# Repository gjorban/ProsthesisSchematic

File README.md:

ProsthesisSchematic
===================

Schematics for Prosthesis PCBs

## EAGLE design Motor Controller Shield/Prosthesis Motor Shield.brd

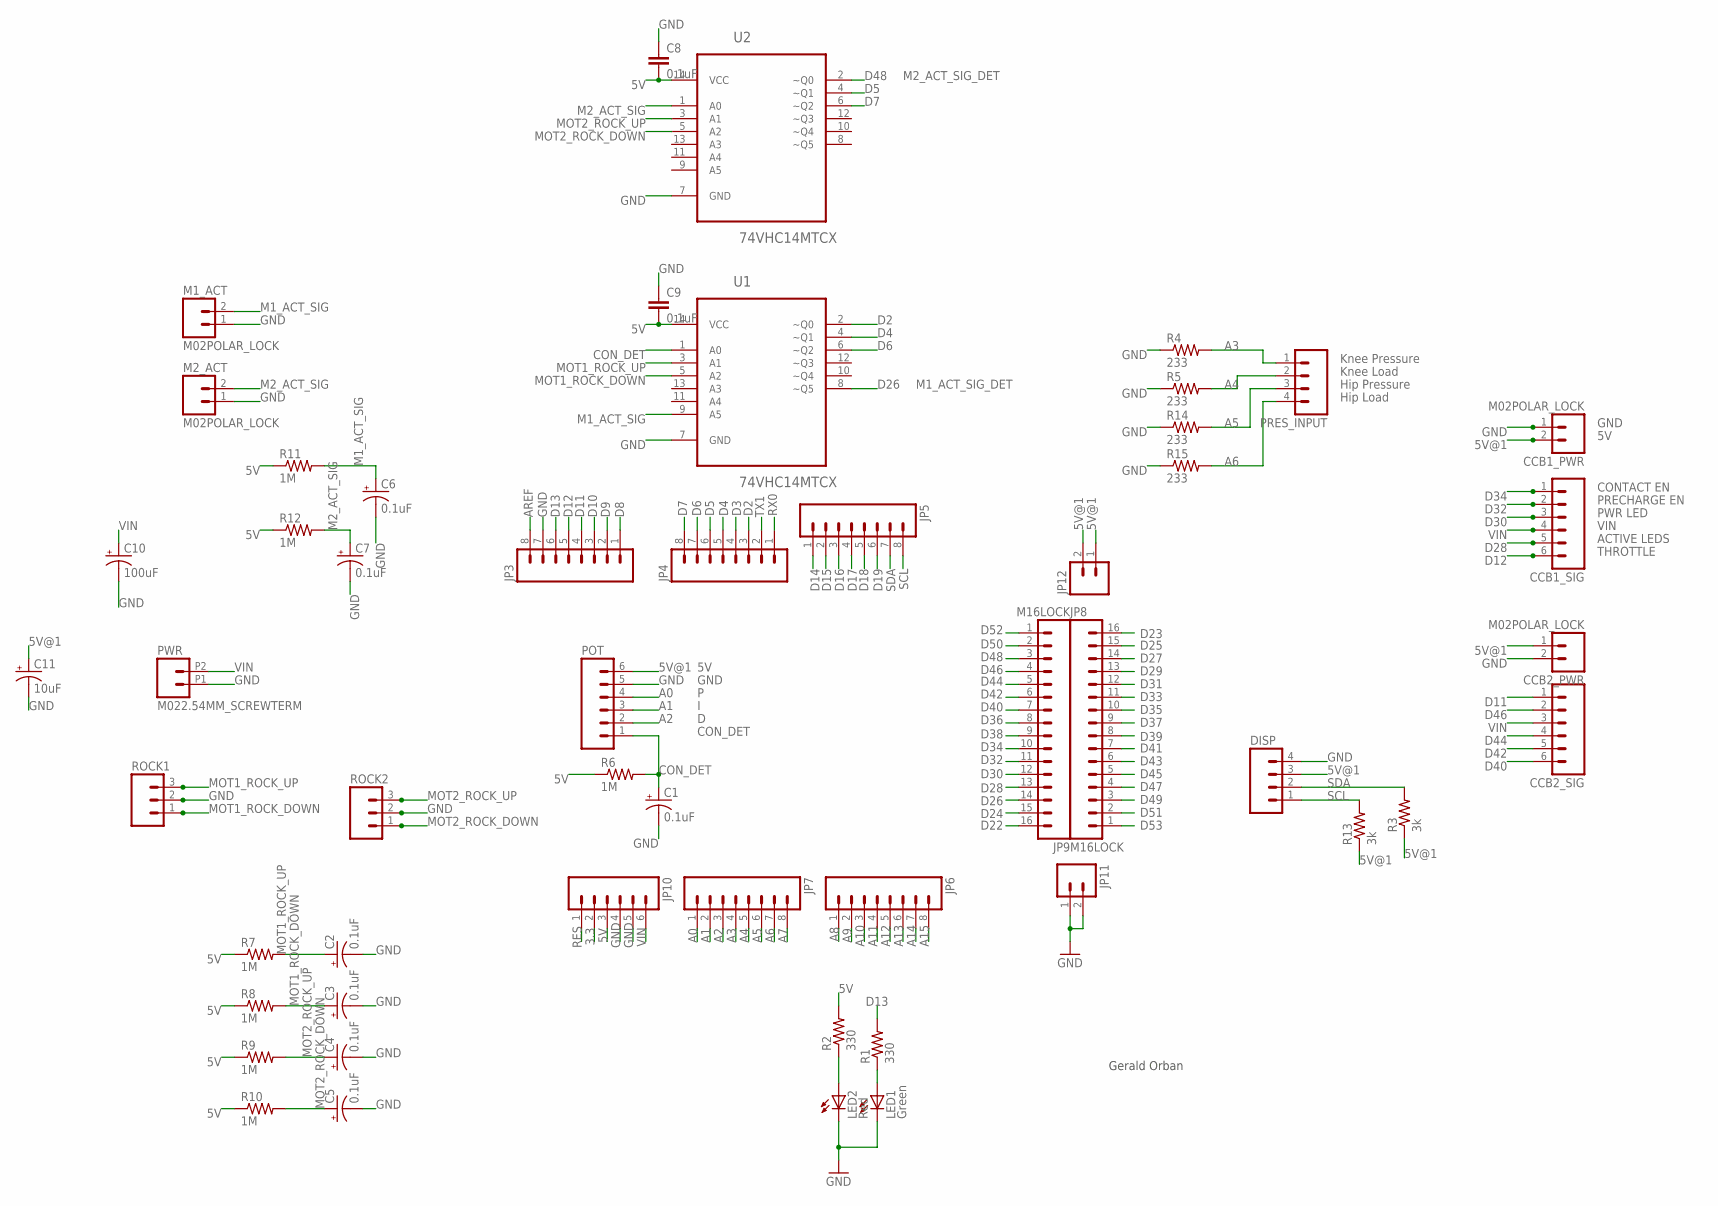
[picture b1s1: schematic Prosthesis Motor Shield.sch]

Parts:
C1, C2, C3, C4, C5, C6, C7: 0.1uF; EIA3216
C8, C9: 0.1uF; 0603-CAP
C10: 100uF; CPOL-RADIAL-100UF-25V
C11: 10uF; CPOL-RADIAL-10UF-25V
CCB1_PWR, CCB2_PWR: M02POLAR_LOCK; MOLEX-1X2_LOCK
CCB1_SIG, CCB2_SIG: M06POLAR_LOCK; MOLEX-1X6_LOCK
DISP: M04POLAR_LOCK; MOLEX-1X4_LOCK
JP3, JP4, JP5, JP6, JP7: M08LOCK; 1X08_LOCK
JP8, JP9: M16LOCK; 1X16_LOCK
JP10: M06LOCK; 1X06_LOCK
JP11, JP12: M02LOCK; 1X02_LOCK
LED1: Green; LED-1206
LED2: Red; LED-1206
M1_ACT, M2_ACT: M02POLAR_LOCK; MOLEX-1X2_LOCK
POT: M06POLAR_LOCK; MOLEX-1X6_LOCK
PRES_INPUT: M04POLAR_LOCK; MOLEX-1X4_LOCK
PWR: M022.54MM_SCREWTERM; 1X02_2.54_SCREWTERM
R1, R2: 330; 0805
R3, R13: 3k; 0603-RES
R4, R5, R14, R15: 233; AXIAL-0.4
R6, R7, R8, R9, R10, R11, R12: 1M; 0603-RES
ROCK1, ROCK2: M03POLAR_LOCK; MOLEX-1X3_LOCK
U1, U2: 74VHC14MTCX; SOP65P640X120-14N

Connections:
3.3: JP10.2
5V: C8.2, C9.2, JP10.3, R2.2, R6.1, R7.1, R8.1, R9.1, R10.1, R11.1, R12.1, U1.14 (VCC), U2.14 (VCC)
5V@1: C11.1 (+), CCB1_PWR.2, CCB2_PWR.1, DISP.3, JP12.1, JP12.2, POT.6, R3.1, R13.1
A0: JP7.1, POT.4
A1: JP7.2, POT.3
A2: JP7.3, POT.2
A3: JP7.4, PRES_INPUT.1, R4.P$2 (2)
A4: JP7.5, PRES_INPUT.2, R5.P$2 (2)
A5: JP7.6, PRES_INPUT.3, R14.P$2 (2)
A6: JP7.7, PRES_INPUT.4, R15.P$2 (2)
A7: JP7.8
A8: JP6.1
A9: JP6.2
A10: JP6.3
A11: JP6.4
A12: JP6.5
A13: JP6.6
A14: JP6.7
A15: JP6.8
AREF: JP3.8
CON_DET: C1.A (+), POT.1, R6.2, U1.1 (A0)
D2: JP4.3, U1.2 (~Q0)
D3: JP4.4
D4: JP4.5, U1.4 (~Q1)
D5: JP4.6, U2.4 (~Q1)
D6: JP4.7, U1.6 (~Q2)
D7: JP4.8, U2.6 (~Q2)
D8: JP3.1
D9: JP3.2
D10: JP3.3
D11: CCB2_SIG.1, JP3.4
D12: CCB1_SIG.6, JP3.5
D13: JP3.6, R1.2
D14: JP5.1
D15: JP5.2
D16: JP5.3
D17: JP5.4
D18: JP5.5
D19: JP5.6
D22: JP9.16
D23: JP8.16
D24: JP9.15
D25: JP8.15
D26: JP9.14, U1.8 (~Q5)
D27: JP8.14
D28: CCB1_SIG.5, JP9.13
D29: JP8.13
D30: CCB1_SIG.3, JP9.12
D31: JP8.12
D32: CCB1_SIG.2, JP9.11
D33: JP8.11
D34: CCB1_SIG.1, JP9.10
D35: JP8.10
D36: JP9.9
D37: JP8.9
D38: JP9.8
D39: JP8.8
D40: CCB2_SIG.6, JP9.7
D41: JP8.7
D42: CCB2_SIG.5, JP9.6
D43: JP8.6
D44: CCB2_SIG.4, JP9.5
D45: JP8.5
D46: CCB2_SIG.2, JP9.4
D47: JP8.4
D48: JP9.3, U2.2 (~Q0)
D49: JP8.3
D50: JP9.2
D51: JP8.2
D52: JP9.1
D53: JP8.1
GND: C1.C (-), C2.C (-), C3.C (-), C4.C (-), C5.C (-), C6.C (-), C7.C (-), C8.1, C9.1, C10.2 (-), C11.2 (-), CCB1_PWR.1, CCB2_PWR.2, DISP.4, JP3.7, JP10.4, JP10.5, JP11.1, JP11.2, LED1.C, LED2.C, M1_ACT.1, M2_ACT.1, POT.5, PWR.P1 (1), R4.P$1 (1), R5.P$1 (1), R14.P$1 (1), R15.P$1 (1), ROCK1.2, ROCK2.2, U1.7 (GND), U2.7 (GND)
M1_ACT_SIG: C6.A (+), M1_ACT.2, R11.2, U1.9 (A5)
M2_ACT_SIG: C7.A (+), M2_ACT.2, R12.2, U2.1 (A0)
MOT1_ROCK_DOWN: C3.A (+), R8.2, ROCK1.1, U1.5 (A2)
MOT1_ROCK_UP: C2.A (+), R7.2, ROCK1.3, U1.3 (A1)
MOT2_ROCK_DOWN: C5.A (+), R10.2, ROCK2.1, U2.5 (A2)
MOT2_ROCK_UP: C4.A (+), R9.2, ROCK2.3, U2.3 (A1)
unnamed: LED2.A, R2.1
unnamed: LED1.A, R1.1
RES: JP10.1
RX0: JP4.1
SCL: DISP.1, JP5.8, R13.2
SDA: DISP.2, JP5.7, R3.2
TX1: JP4.2
VIN: C10.1 (+), CCB1_SIG.4, CCB2_SIG.3, JP10.6, PWR.P2 (2)

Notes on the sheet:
Gerald Orban
THROTTLE
ACTIVE LEDS
VIN
PWR LED
PRECHARGE EN
CONTACT EN
GND
CON_DET
Knee Pressure
Knee Load
Hip Pressure
Hip Load
M2_ACT_SIG_DET
M1_ACT_SIG_DET

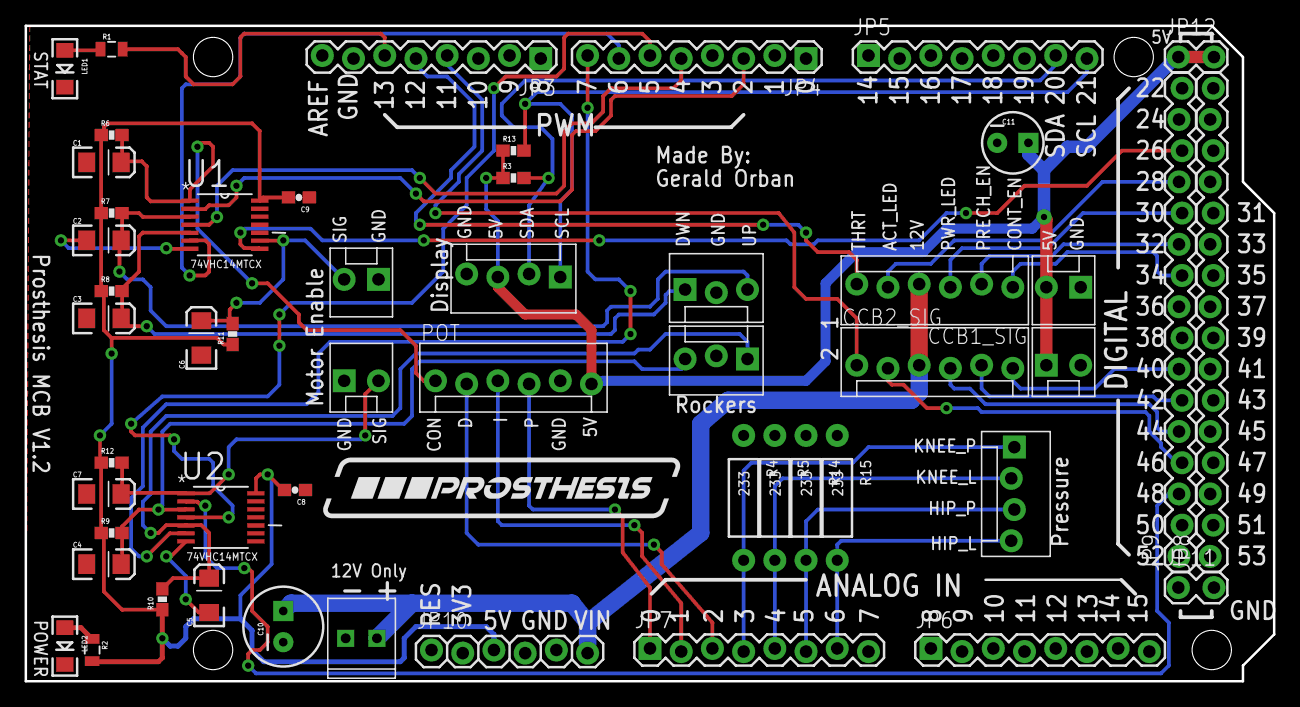
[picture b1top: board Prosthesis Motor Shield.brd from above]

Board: 2 copper layers, 101.6 x 53.3 mm, 53 parts (0 on the bottom side), 40 nets.

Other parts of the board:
U$1: PROS_LOGO

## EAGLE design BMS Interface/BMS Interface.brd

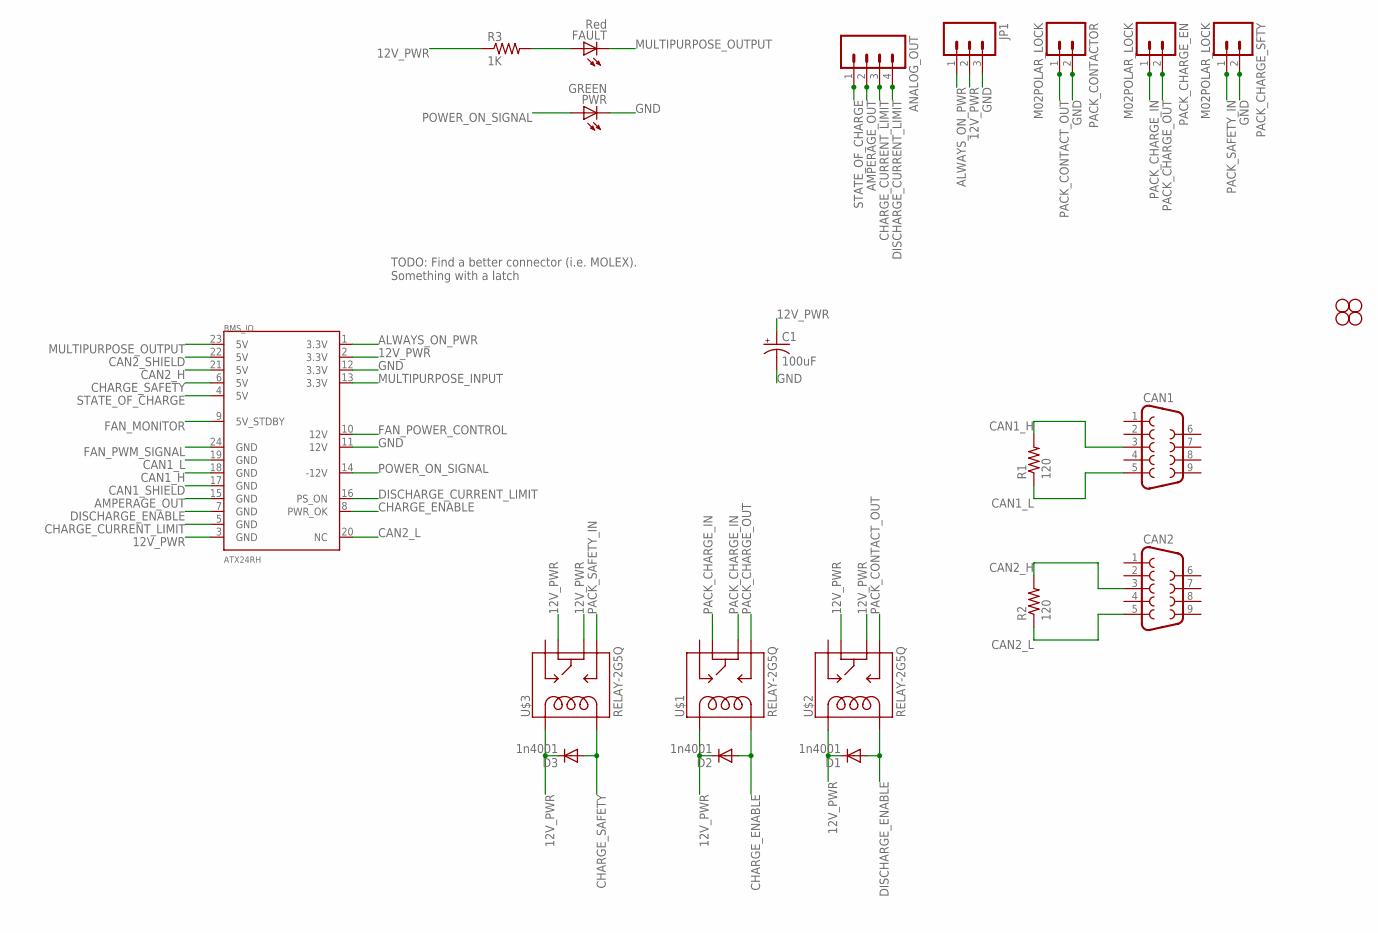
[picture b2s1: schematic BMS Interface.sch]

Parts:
ANALOG_OUT: M04POLAR_LOCK; MOLEX-1X4_LOCK
BMS_IO: ATX24RH; ATX24_RIGHT_ANGLE
C1: 100uF; CPOL-RADIAL-100UF-25V
CAN1, CAN2: DB9FEMALE; DB9
D1, D2, D3: 1n4001; SMA-DIODE
FAULT: Red; LED5MM
JP1: M03SCREW; SCREWTERMINAL-3.5MM-3
PACK_CHARGE_EN: M02POLAR_LOCK; MOLEX-1X2_LOCK
PACK_CHARGE_SFTY: M02POLAR_LOCK; MOLEX-1X2_LOCK
PACK_CONTACTOR: M02POLAR_LOCK; MOLEX-1X2_LOCK
PWR: GREEN; LED5MM
R1, R2: 120; 0603-RES
R3: 1K; 0805
STANDOFF1, STANDOFF2, STANDOFF3, STANDOFF4: STAND-OFF
U$1, U$2, U$3: RELAY-2G5Q; RELAY-G5V

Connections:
12V_PWR: BMS_IO.2 (3.3V), BMS_IO.3 (GND), C1.1 (+), D1.C, D2.C, D3.C, JP1.2, R3.1, U$1.2, U$2.2, U$2.5, U$2.6, U$3.2, U$3.5, U$3.6
ALWAYS_ON_PWR: BMS_IO.1 (3.3V), JP1.1
AMPERAGE_OUT: ANALOG_OUT.2, BMS_IO.15 (GND)
CAN1_H: BMS_IO.18 (GND), CAN1.3, R1.2
CAN1_L: BMS_IO.19 (GND), CAN1.5, R1.1
CAN1_SHIELD: BMS_IO.17 (GND)
CAN2_H: BMS_IO.21 (5V), CAN2.3, R2.2
CAN2_L: BMS_IO.20 (NC), CAN2.5, R2.1
CAN2_SHIELD: BMS_IO.22 (5V)
CHARGE_CURRENT_LIMIT: ANALOG_OUT.3, BMS_IO.5 (GND)
CHARGE_ENABLE: BMS_IO.8 (PWR_OK), D2.A, U$1.9
CHARGE_SAFETY: BMS_IO.6 (5V), D3.A, U$3.9
DISCHARGE_CURRENT_LIMIT: ANALOG_OUT.4, BMS_IO.16 (PS_ON)
DISCHARGE_ENABLE: BMS_IO.7 (GND), D1.A, U$2.9
FAN_MONITOR: BMS_IO.9 (5V_STDBY)
FAN_POWER_CONTROL: BMS_IO.10 (12V)
FAN_PWM_SIGNAL: BMS_IO.24 (GND)
GND: BMS_IO.11 (12V), BMS_IO.12 (3.3V), C1.2 (-), JP1.3, PACK_CHARGE_SFTY.2, PACK_CONTACTOR.2, PWR.K (C)
MULTIPURPOSE_INPUT: BMS_IO.13 (3.3V)
MULTIPURPOSE_OUTPUT: BMS_IO.23 (5V), FAULT.K (C)
unnamed: FAULT.A, R3.2
PACK_CHARGE_IN: PACK_CHARGE_EN.1, U$1.5, U$1.6
PACK_CHARGE_OUT: PACK_CHARGE_EN.2, U$1.10
PACK_CONTACT_OUT: PACK_CONTACTOR.1, U$2.10
PACK_SAFETY_IN: PACK_CHARGE_SFTY.1, U$3.10
POWER_ON_SIGNAL: BMS_IO.14 (-12V), PWR.A
STATE_OF_CHARGE: ANALOG_OUT.1, BMS_IO.4 (5V)

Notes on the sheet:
TODO: Find a better connector (i.e. MOLEX). Something with a latch

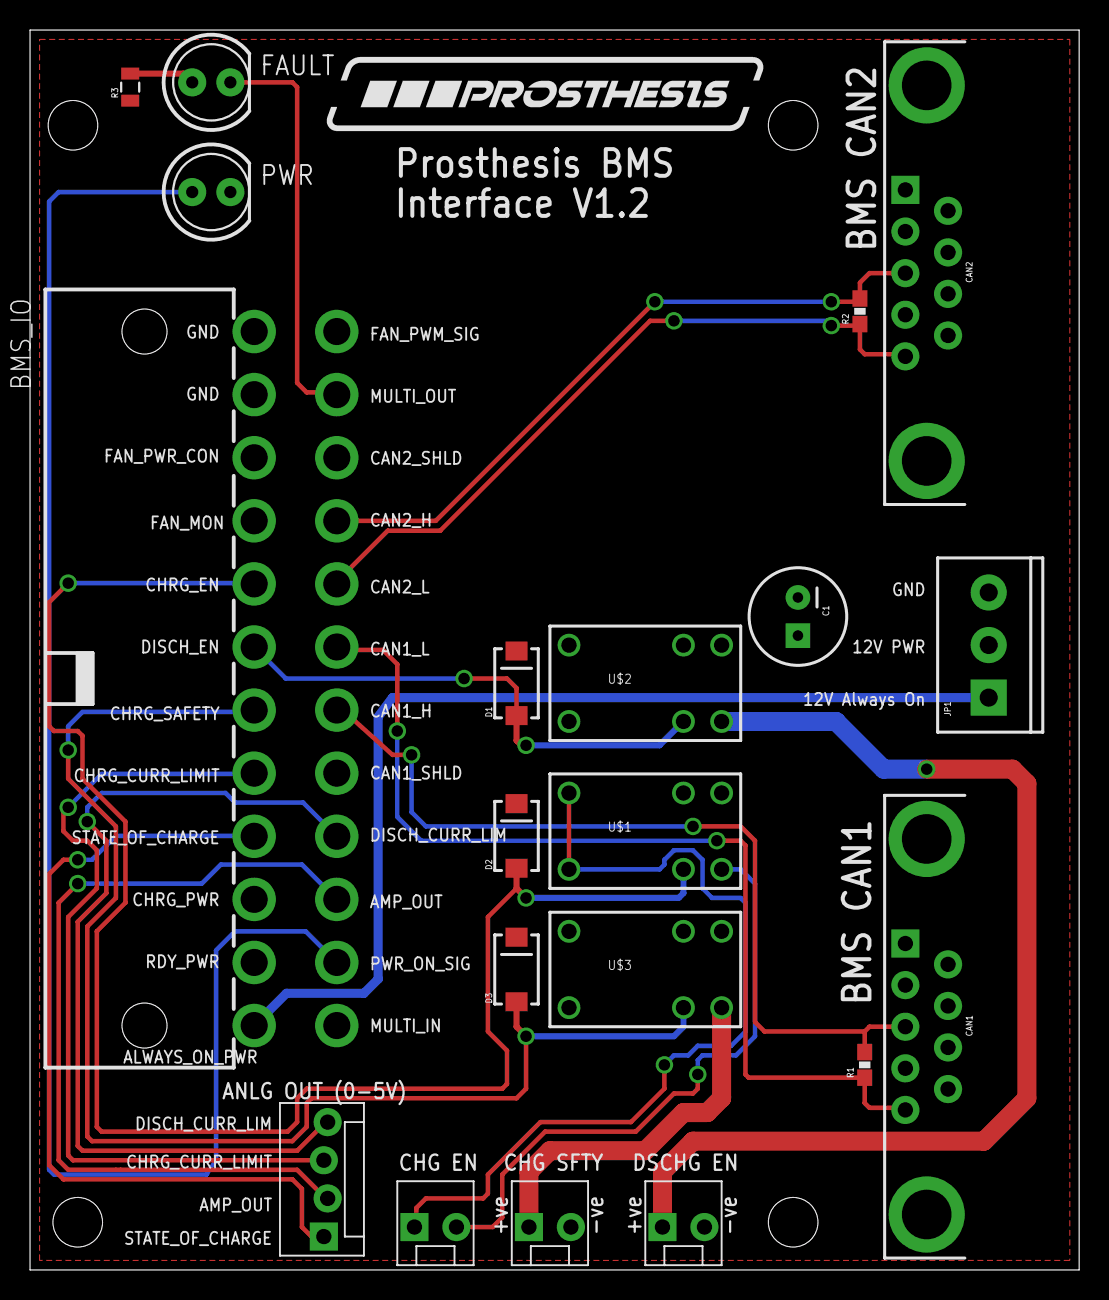
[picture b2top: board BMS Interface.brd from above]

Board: 2 copper layers, 69.8 x 82.5 mm, 25 parts (0 on the bottom side), 21 nets.

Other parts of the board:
U$4: PROS_LOGO

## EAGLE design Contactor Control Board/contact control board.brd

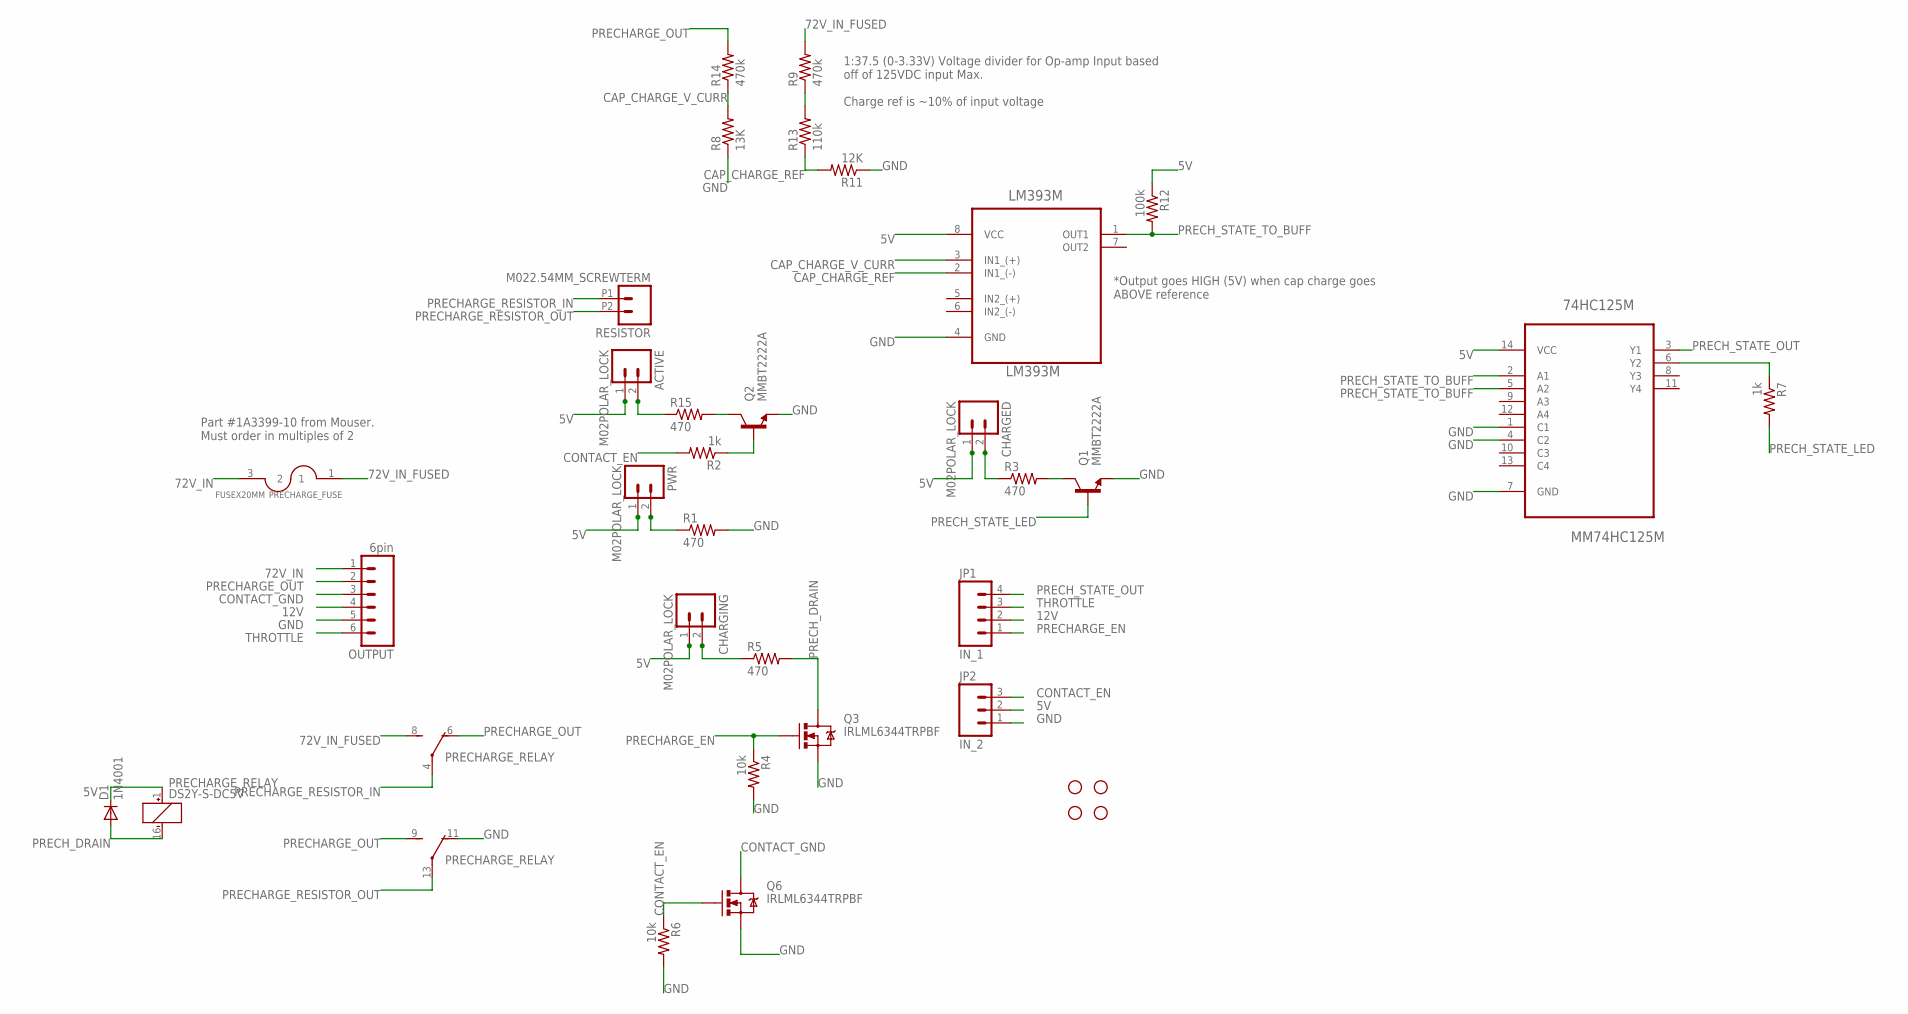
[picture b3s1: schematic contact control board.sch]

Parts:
74HC125M: MM74HC125M; SOIC127P600X175-14N
ACTIVE: M02POLAR_LOCK; MOLEX-1X2_LOCK
CHARGED: M02POLAR_LOCK; MOLEX-1X2_LOCK
CHARGING: M02POLAR_LOCK; MOLEX-1X2_LOCK
D1: 1N4001; DIODE-1N4001
JP1: IN_1; MOLEX-1X4_LOCK
JP2: IN_2; MOLEX-1X3_LOCK
LM393M: LM393M; SOIC127P600X180-8N
OUTPUT: 6pin; SCREWTERMINAL-3.5MM-6
PRECHARGE_FUSE: FUSEX20MM; FUSE_5MM
PRECHARGE_RELAY: DS2Y-S-DC5V; DS2Y
PWR: M02POLAR_LOCK; MOLEX-1X2_LOCK
Q1, Q2: MMBT2222A; SOT23
Q3, Q6: IRLML6344TRPBF; SOT23
R1, R3, R5, R15: 470; 0805
R2, R7: 1k; 0603-RES
R4, R6: 10k; 0603-RES
R8: 13K; 0805
R9, R14: 470k; 0805
R11: 12K; 0805
R12: 100k; 0603-RES
R13: 110k; 0805
RESISTOR: M022.54MM_SCREWTERM; 1X02_2.54_SCREWTERM
STANDOFF1, STANDOFF2, STANDOFF3, STANDOFF4: STAND-OFF

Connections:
5V: 74HC125M.14 (VCC), ACTIVE.1, CHARGED.1, CHARGING.1, D1.C, JP2.2, LM393M.8 (VCC), PRECHARGE_RELAY.1 (+), PWR.1, R12.1
12V: JP1.2, OUTPUT.4
72V_IN: OUTPUT.1, PRECHARGE_FUSE.3 (2)
72V_IN_FUSED: PRECHARGE_FUSE.1, PRECHARGE_RELAY.8 (S), R9.2
CAP_CHARGE_REF: LM393M.2 (IN1_(-)), R11.2, R13.1
CAP_CHARGE_V_CURR: LM393M.3 (IN1_(+)), R8.2, R14.1
CONTACT_EN: JP2.3, Q6.1 (G), R2.2, R6.1
CONTACT_GND: OUTPUT.3, Q6.3 (D)
GND: 74HC125M.1 (C1), 74HC125M.4 (C2), 74HC125M.7 (GND), JP2.1, LM393M.4 (GND), OUTPUT.5, PRECHARGE_RELAY.11 (O), Q1.2 (E), Q2.2 (E), Q3.2 (S), Q6.2 (S), R1.2, R4.2, R6.2, R8.1, R11.1
unnamed: Q2.3 (C), R15.2
unnamed: Q2.1 (B), R2.1
unnamed: R9.1, R13.2
unnamed: CHARGED.2, R3.1
unnamed: Q1.3 (C), R3.2
unnamed: 74HC125M.6 (Y2), R7.1
unnamed: CHARGING.2, R5.1
unnamed: ACTIVE.2, R15.1
unnamed: PWR.2, R1.1
PRECHARGE_EN: JP1.1, Q3.1 (G), R4.1
PRECHARGE_OUT: OUTPUT.2, PRECHARGE_RELAY.6 (O), PRECHARGE_RELAY.9 (S), R14.2
PRECHARGE_RESISTOR_IN: PRECHARGE_RELAY.4, RESISTOR.P1 (1)
PRECHARGE_RESISTOR_OUT: PRECHARGE_RELAY.13, RESISTOR.P2 (2)
PRECH_DRAIN: D1.A, PRECHARGE_RELAY.16 (-), Q3.3 (D), R5.2
PRECH_STATE_LED: Q1.1 (B), R7.2
PRECH_STATE_OUT: 74HC125M.3 (Y1), JP1.4
PRECH_STATE_TO_BUFF: 74HC125M.2 (A1), 74HC125M.5 (A2), LM393M.1 (OUT1), R12.2
THROTTLE: JP1.3, OUTPUT.6

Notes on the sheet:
1:37.5 (0-3.33V) Voltage divider for Op-amp Input based off of 125VDC input Max. Charge ref is ~10% of input voltage
*Output goes HIGH (5V) when cap charge goes ABOVE reference
Part #1A3399-10 from Mouser. Must order in multiples of 2

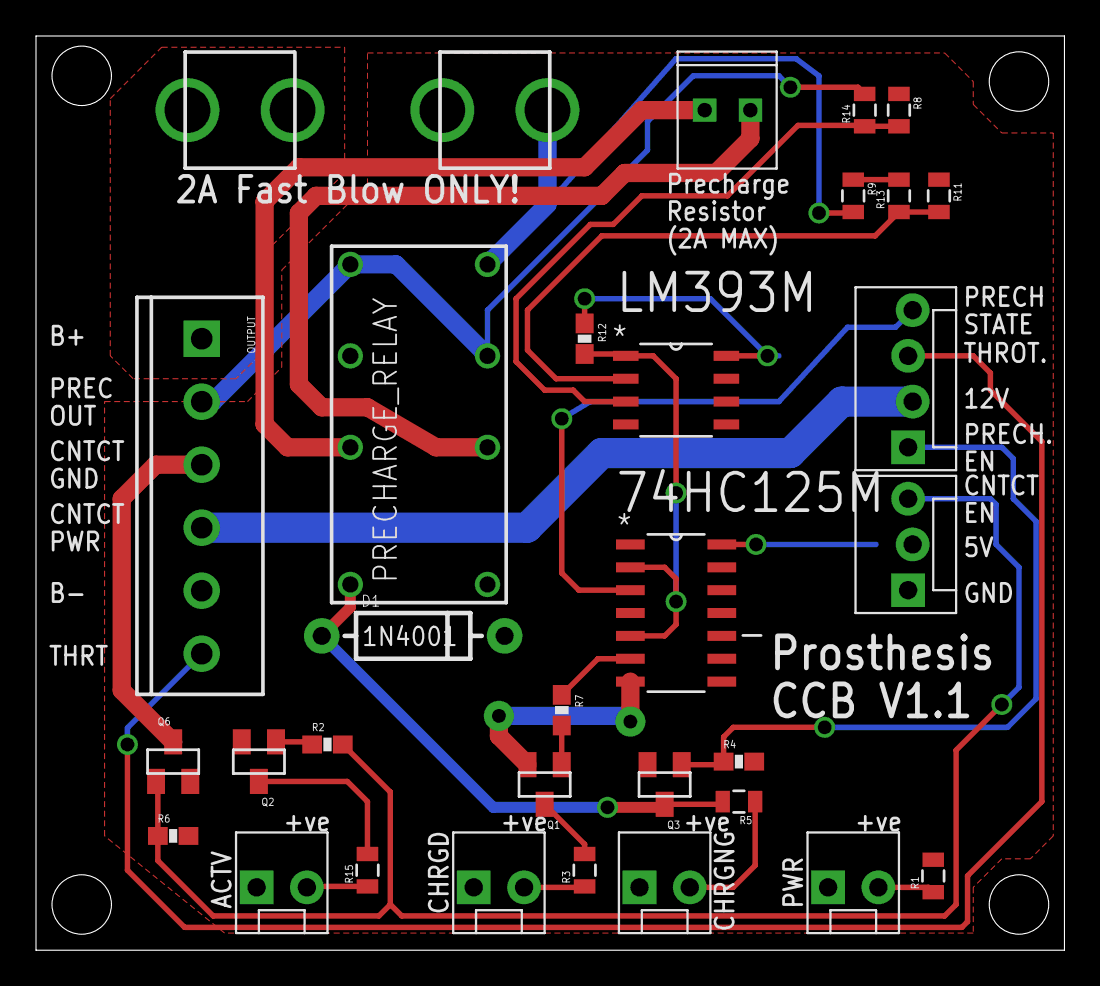
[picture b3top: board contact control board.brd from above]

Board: 2 copper layers, 57.1 x 50.8 mm, 35 parts (0 on the bottom side), 27 nets.

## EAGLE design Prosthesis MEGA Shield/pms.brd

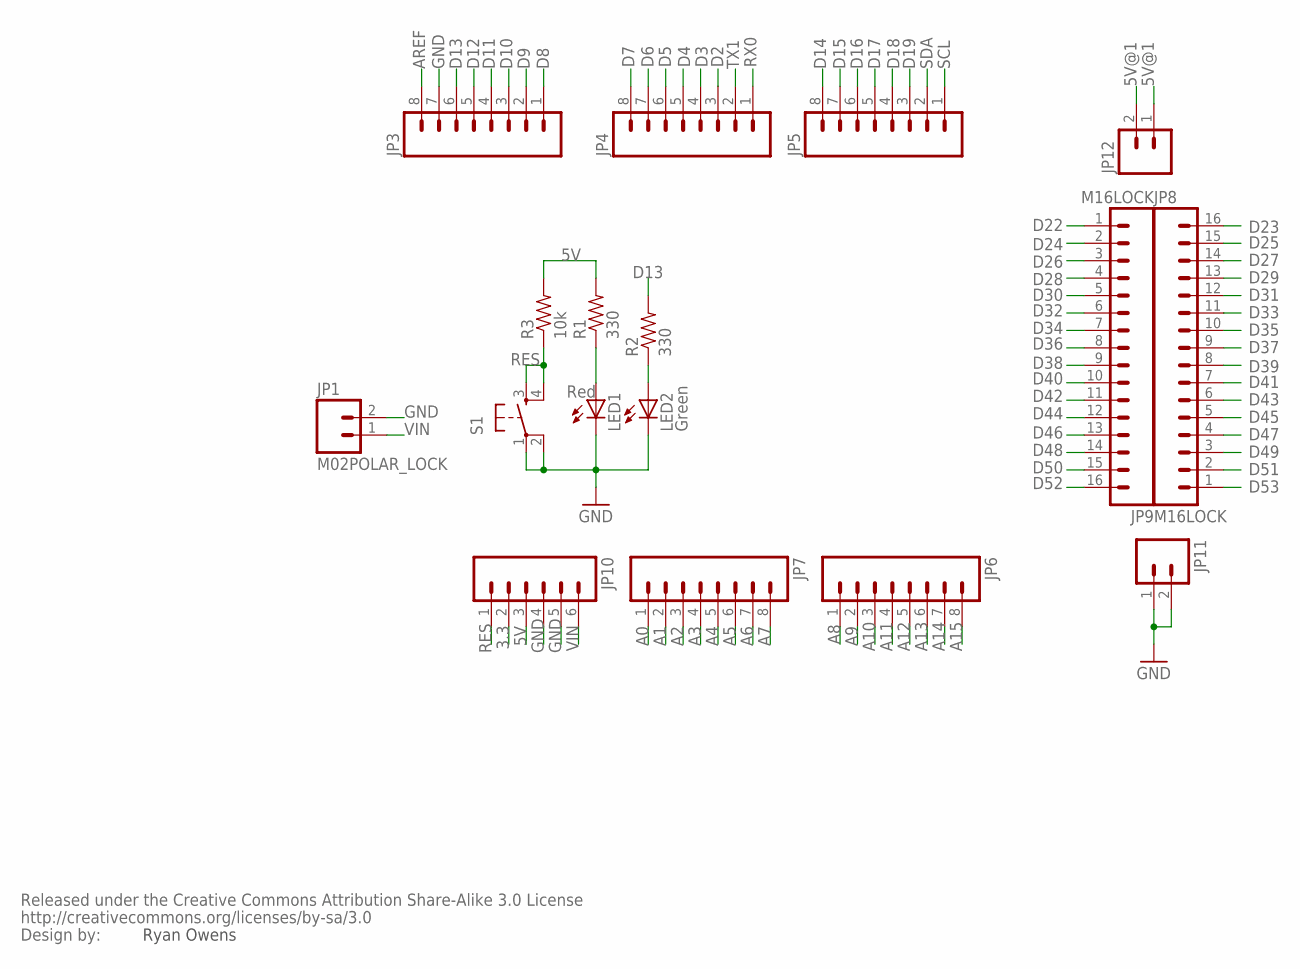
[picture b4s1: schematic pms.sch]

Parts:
JP1: M02POLAR_LOCK; MOLEX-1X2_LOCK
JP3, JP4, JP5, JP6, JP7: M08LOCK; 1X08_LOCK
JP8, JP9: M16LOCK; 1X16_LOCK
JP10: M06LOCK; 1X06_LOCK
JP11, JP12: M02LOCK; 1X02_LOCK
LED1: Red; LED5MM
LED2: Green; LED5MM
R1, R2: 330; AXIAL-0.3
R3: 10k; AXIAL-0.3
S1: TAC_SWITCHPTH; TACTILE-PTH
U$2: CREATIVE_COMMONS

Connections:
3.3: JP10.2
5V: JP10.3, R1.P$2 (2), R3.P$2 (2)
5V@1: JP12.1, JP12.2
A0: JP7.1
A1: JP7.2
A2: JP7.3
A3: JP7.4
A4: JP7.5
A5: JP7.6
A6: JP7.7
A7: JP7.8
A8: JP6.1
A9: JP6.2
A10: JP6.3
A11: JP6.4
A12: JP6.5
A13: JP6.6
A14: JP6.7
A15: JP6.8
AREF: JP3.8
D2: JP4.3
D3: JP4.4
D4: JP4.5
D5: JP4.6
D6: JP4.7
D7: JP4.8
D8: JP3.1
D9: JP3.2
D10: JP3.3
D11: JP3.4
D12: JP3.5
D13: JP3.6, R2.P$2 (2)
D14: JP5.8
D15: JP5.7
D16: JP5.6
D17: JP5.5
D18: JP5.4
D19: JP5.3
D22: JP9.1
D23: JP8.16
D24: JP9.2
D25: JP8.15
D26: JP9.3
D27: JP8.14
D28: JP9.4
D29: JP8.13
D30: JP9.5
D31: JP8.12
D32: JP9.6
D33: JP8.11
D34: JP9.7
D35: JP8.10
D36: JP9.8
D37: JP8.9
D38: JP9.9
D39: JP8.8
D40: JP9.10
D41: JP8.7
D42: JP9.11
D43: JP8.6
D44: JP9.12
D45: JP8.5
D46: JP9.13
D47: JP8.4
D48: JP9.14
D49: JP8.3
D50: JP9.15
D51: JP8.2
D52: JP9.16
D53: JP8.1
GND: JP1.2, JP3.7, JP10.4, JP10.5, JP11.1, JP11.2, LED1.K (C), LED2.K (C), S1.1, S1.2
unnamed: LED1.A, R1.P$1 (1)
unnamed: LED2.A, R2.P$1 (1)
RES: JP10.1, R3.P$1 (1), S1.3, S1.4
RX0: JP4.1
SCL: JP5.1
SDA: JP5.2
TX1: JP4.2
VIN: JP1.1, JP10.6

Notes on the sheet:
Ryan Owens

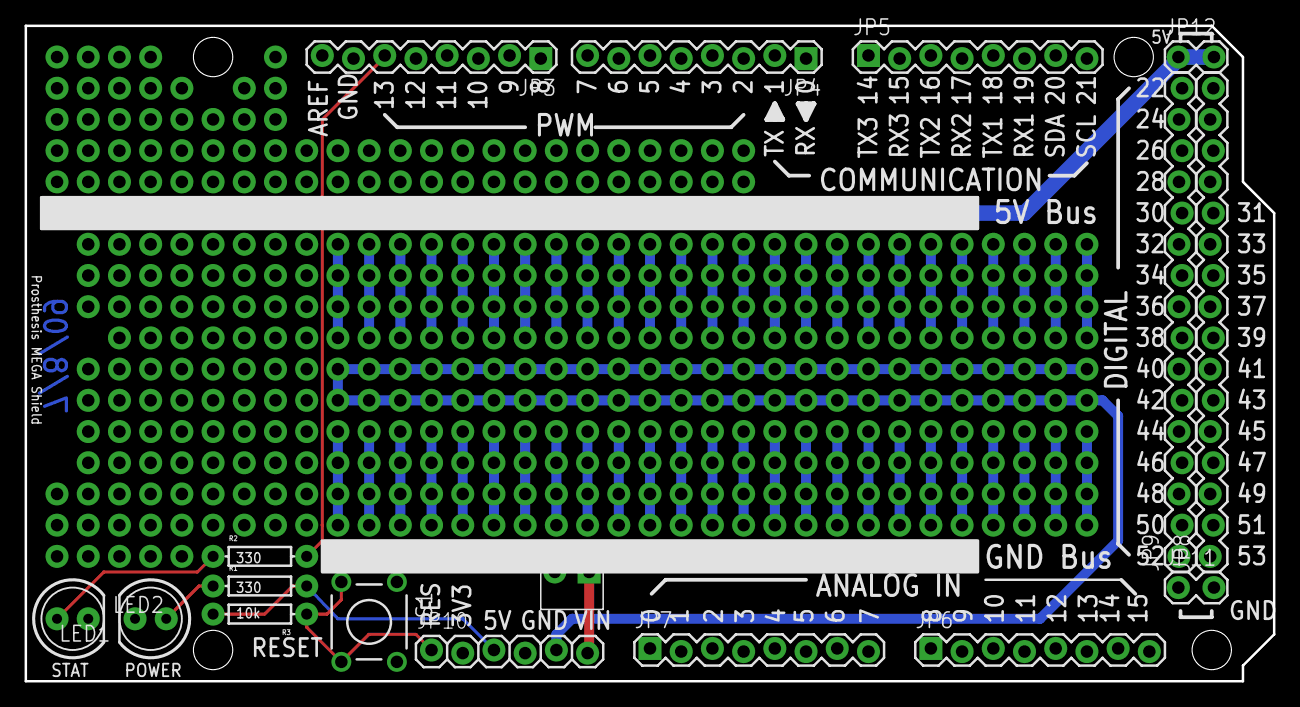
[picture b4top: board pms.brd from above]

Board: 2 copper layers, 101.6 x 53.3 mm, 18 parts (0 on the bottom side), 8 nets.

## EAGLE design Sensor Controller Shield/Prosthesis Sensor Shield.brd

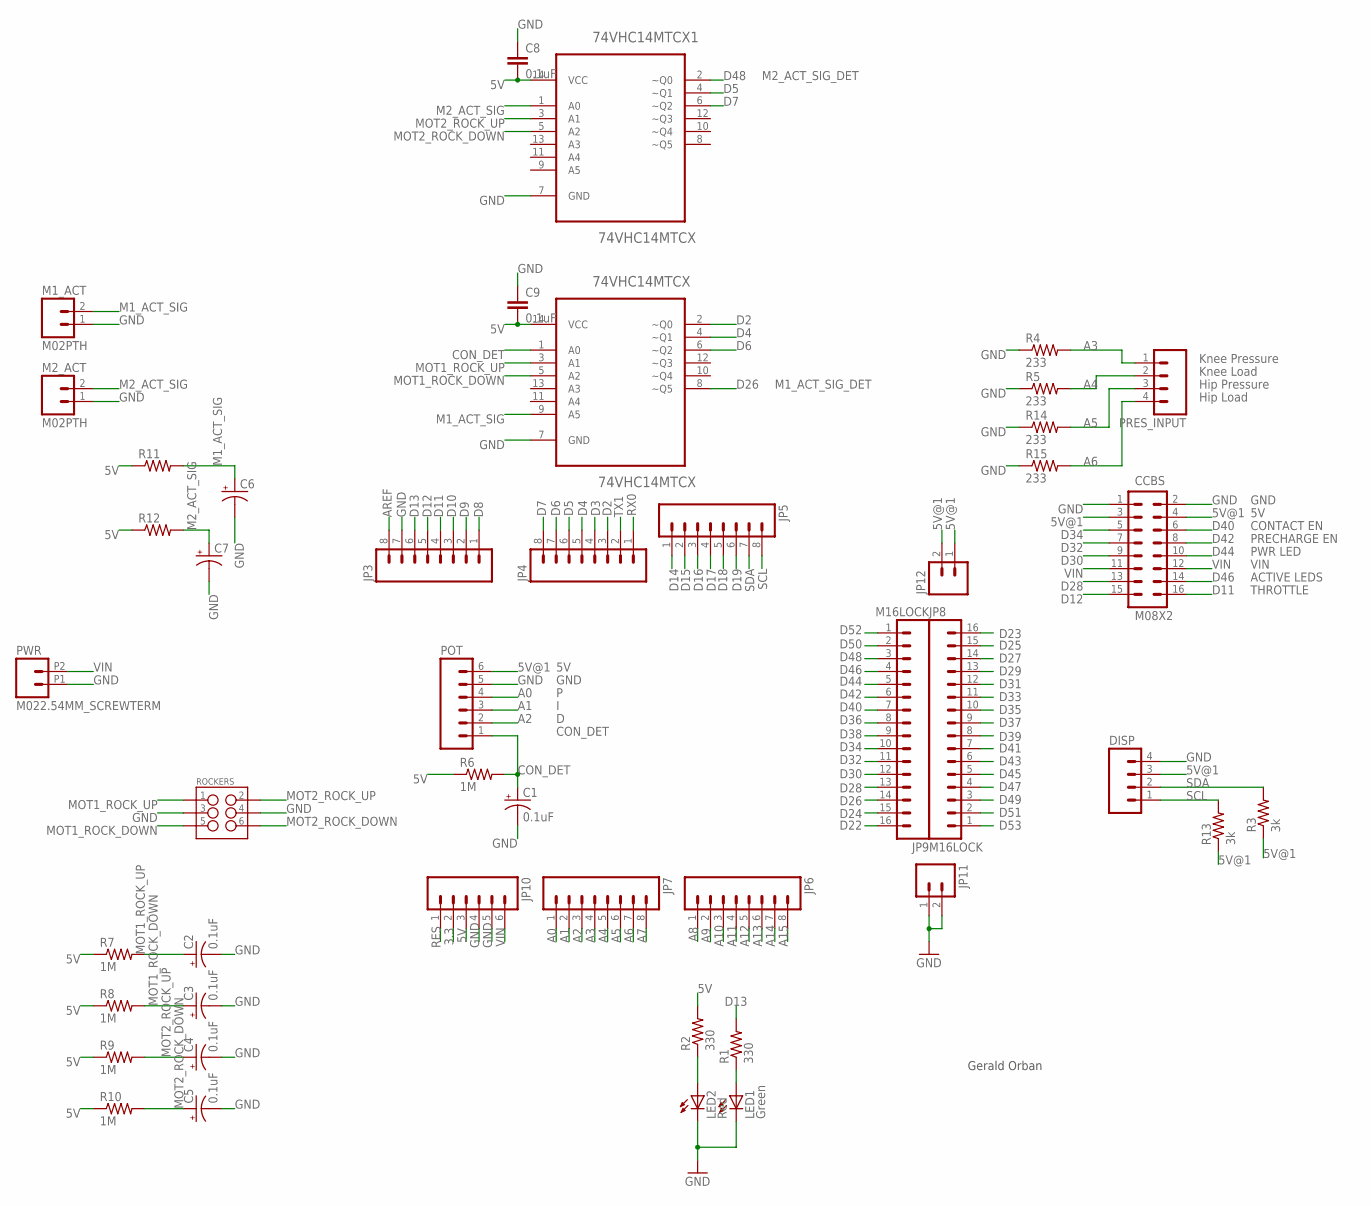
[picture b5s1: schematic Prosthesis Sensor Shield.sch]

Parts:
74VHC14MTCX, 74VHC14MTCX1: 74VHC14MTCX; SOP65P640X120-14N
C1, C2, C3, C4, C5: 0.1uF; EIA3216
C6, C7: CAP_POL1206; EIA3216
C8, C9: 0.1uF; 0603-CAP
CCBS: M08X2; 2X8
DISP: M04PTH; 1X04
JP3, JP4, JP5, JP6, JP7: M08LOCK; 1X08_LOCK
JP8, JP9: M16LOCK; 1X16_LOCK
JP10: M06LOCK; 1X06_LOCK
JP11, JP12: M02LOCK; 1X02_LOCK
LED1: Green; LED-1206
LED2: Red; LED-1206
M1_ACT, M2_ACT: M02PTH; 1X02
POT: M06SIP; 1X06
PRES_INPUT: M04PTH; 1X04
PWR: M022.54MM_SCREWTERM; 1X02_2.54_SCREWTERM
R1, R2: 330; 0603-RES
R3, R13: 3k; 0603-RES
R4, R5, R14, R15: 233; AXIAL-0.4
R6, R7, R8, R9, R10: 1M; 0603-RES
R11, R12: RESISTOR0603; 0603-RES
ROCKERS: M03X22X3_SILK_SM; 2X3

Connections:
3.3: JP10.2
5V: 74VHC14MTCX.14 (VCC), 74VHC14MTCX1.14 (VCC), C8.2, C9.2, JP10.3, R2.2, R6.1, R7.1, R8.1, R9.1, R10.1, R11.1, R12.1
5V@1: CCBS.3, CCBS.4, DISP.3, JP12.1, JP12.2, POT.6, R3.1, R13.1
A0: JP7.1, POT.4
A1: JP7.2, POT.3
A2: JP7.3, POT.2
A3: JP7.4, PRES_INPUT.1, R4.P$2 (2)
A4: JP7.5, PRES_INPUT.2, R5.P$2 (2)
A5: JP7.6, PRES_INPUT.3, R14.P$2 (2)
A6: JP7.7, PRES_INPUT.4, R15.P$2 (2)
A7: JP7.8
A8: JP6.1
A9: JP6.2
A10: JP6.3
A11: JP6.4
A12: JP6.5
A13: JP6.6
A14: JP6.7
A15: JP6.8
AREF: JP3.8
CON_DET: 74VHC14MTCX.1 (A0), C1.A (+), POT.1, R6.2
D2: 74VHC14MTCX.2 (~Q0), JP4.3
D3: JP4.4
D4: 74VHC14MTCX.4 (~Q1), JP4.5
D5: 74VHC14MTCX1.4 (~Q1), JP4.6
D6: 74VHC14MTCX.6 (~Q2), JP4.7
D7: 74VHC14MTCX1.6 (~Q2), JP4.8
D8: JP3.1
D9: JP3.2
D10: JP3.3
D11: CCBS.16, JP3.4
D12: CCBS.15, JP3.5
D13: JP3.6, R1.2
D14: JP5.1
D15: JP5.2
D16: JP5.3
D17: JP5.4
D18: JP5.5
D19: JP5.6
D22: JP9.16
D23: JP8.16
D24: JP9.15
D25: JP8.15
D26: 74VHC14MTCX.8 (~Q5), JP9.14
D27: JP8.14
D28: CCBS.13, JP9.13
D29: JP8.13
D30: CCBS.9, JP9.12
D31: JP8.12
D32: CCBS.7, JP9.11
D33: JP8.11
D34: CCBS.5, JP9.10
D35: JP8.10
D36: JP9.9
D37: JP8.9
D38: JP9.8
D39: JP8.8
D40: CCBS.6, JP9.7
D41: JP8.7
D42: CCBS.8, JP9.6
D43: JP8.6
D44: CCBS.10, JP9.5
D45: JP8.5
D46: CCBS.14, JP9.4
D47: JP8.4
D48: 74VHC14MTCX1.2 (~Q0), JP9.3
D49: JP8.3
D50: JP9.2
D51: JP8.2
D52: JP9.1
D53: JP8.1
GND: 74VHC14MTCX.7 (GND), 74VHC14MTCX1.7 (GND), C1.C (-), C2.C (-), C3.C (-), C4.C (-), C5.C (-), C6.C (-), C7.C (-), C8.1, C9.1, CCBS.1, CCBS.2, DISP.4, JP3.7, JP10.4, JP10.5, JP11.1, JP11.2, LED1.C, LED2.C, M1_ACT.1, M2_ACT.1, POT.5, PWR.P1 (1), R4.P$1 (1), R5.P$1 (1), R14.P$1 (1), R15.P$1 (1), ROCKERS.3, ROCKERS.4
M1_ACT_SIG: 74VHC14MTCX.9 (A5), C6.A (+), M1_ACT.2, R11.2
M2_ACT_SIG: 74VHC14MTCX1.1 (A0), C7.A (+), M2_ACT.2, R12.2
MOT1_ROCK_DOWN: 74VHC14MTCX.5 (A2), C3.A (+), R8.2, ROCKERS.5
MOT1_ROCK_UP: 74VHC14MTCX.3 (A1), C2.A (+), R7.2, ROCKERS.1
MOT2_ROCK_DOWN: 74VHC14MTCX1.5 (A2), C5.A (+), R10.2, ROCKERS.6
MOT2_ROCK_UP: 74VHC14MTCX1.3 (A1), C4.A (+), R9.2, ROCKERS.2
unnamed: LED2.A, R2.1
unnamed: LED1.A, R1.1
RES: JP10.1
RX0: JP4.1
SCL: DISP.1, JP5.8, R13.2
SDA: DISP.2, JP5.7, R3.2
TX1: JP4.2
VIN: CCBS.11, CCBS.12, JP10.6, PWR.P2 (2)

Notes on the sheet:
Gerald Orban
THROTTLE
ACTIVE LEDS
VIN
PWR LED
PRECHARGE EN
CONTACT EN
GND
CON_DET
Knee Pressure
Knee Load
Hip Pressure
Hip Load
M2_ACT_SIG_DET
M1_ACT_SIG_DET

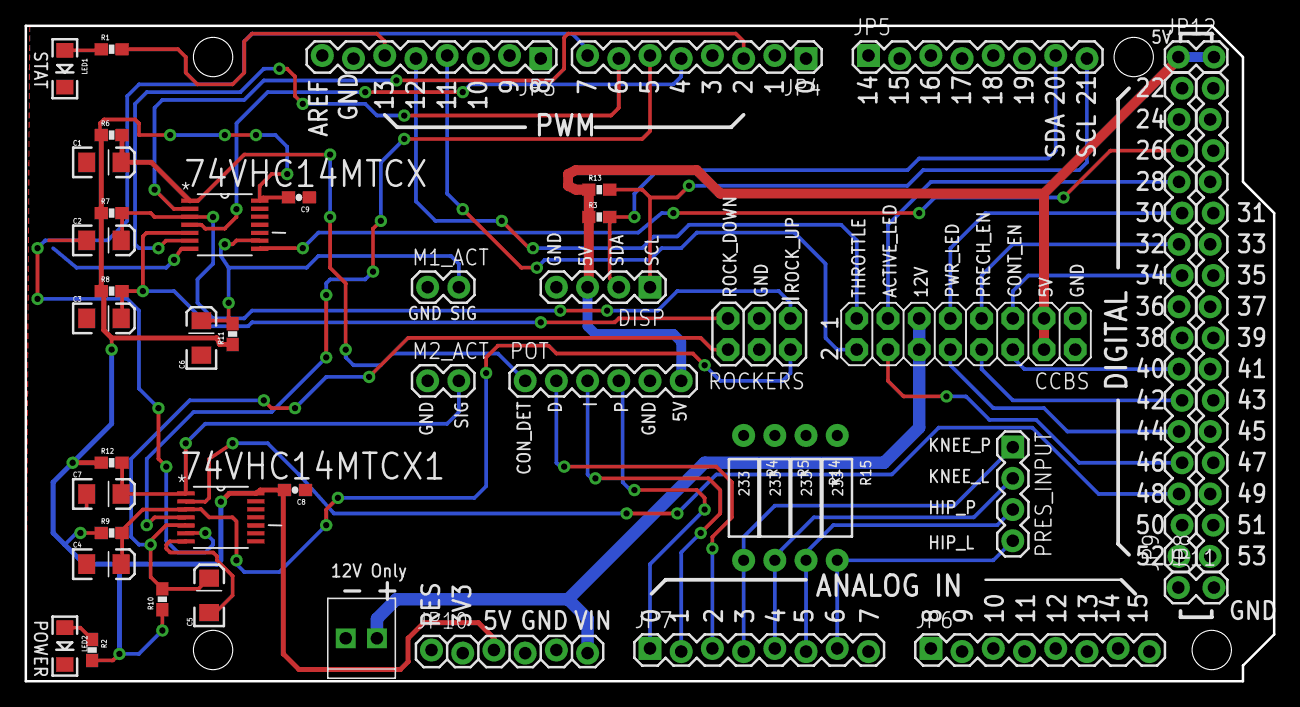
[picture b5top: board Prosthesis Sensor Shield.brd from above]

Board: 2 copper layers, 101.6 x 53.3 mm, 46 parts (0 on the bottom side), 40 nets.

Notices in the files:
parts and their libraries:
SparkFun-Connectors: Licensing: CC v3.0 Share-Alike You are welcome to use this library for commercial purposes.
SparkFun: Released under the Creative Commons Attribution Share-Alike 3.0 License
SparkFun: http://creativecommons.org/licenses/by-sa/3.0
